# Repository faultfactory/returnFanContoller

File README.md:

# returnFanContoller

### Problem: 

My house has an issue with stratification in the summer, requiring us to leave a fan in the stairwell. I saw this potentially coming from talking to my neighbors and in addition to good insulation on the roof deck, I also installed a return air duct on the 2nd floor (which it did not have).  This duct is very high in the room and with a proper draw should evacuate hot air in the room quickly with the right amount of negative pressure applied. Because the return ducts in the house start with a (very poorly sealed) run of panning through joist bays and the duct takes a circuitous path upstairs, I am confident I am getting very little, if any draw from the return duct I connected to the 2nd floor.  To remedy this I have purchased a [Fantech ProAir EC-6](https://shop.fantech.net/en-US/prioair--6--ec--inline--duct--fan/p96222#!) I chose this because I would rather not play around with dampers if I can help it.  My furnace is not intended to integrate  with any sort of external fan, nor is my thermostat (nest... maybe 2nd gen?). 

### Goals: 

1. Log the activity of the 24VAC thermostat signals coming from the Nest. Also log the blower fan speeds and some relevant temperatures. 
2. Activate the booster fan when the furnace fan runs.
3. Monitor a temp sensor on the second floor and activate both the furnace and booster fan when the temperature differential exceeds a threshold. 

~~This repostitory consists of the code for the controller which will run on a raspberry pi. Schematics / BOM  will be on a separate hackaday.io project when time permits.~~

This project has been completed and I am in the process of documenting it. Overwhelming success. However, it was exceptionally difficult to get a proper PWM generated out of the raspberry pi and over time it just became more trouble than it was worth to stay with that platform. I've moved the effort to an Arduino which worked fine. I am still going to attempt to add some of the bells and whistles I wanted earlier but for now it works great.

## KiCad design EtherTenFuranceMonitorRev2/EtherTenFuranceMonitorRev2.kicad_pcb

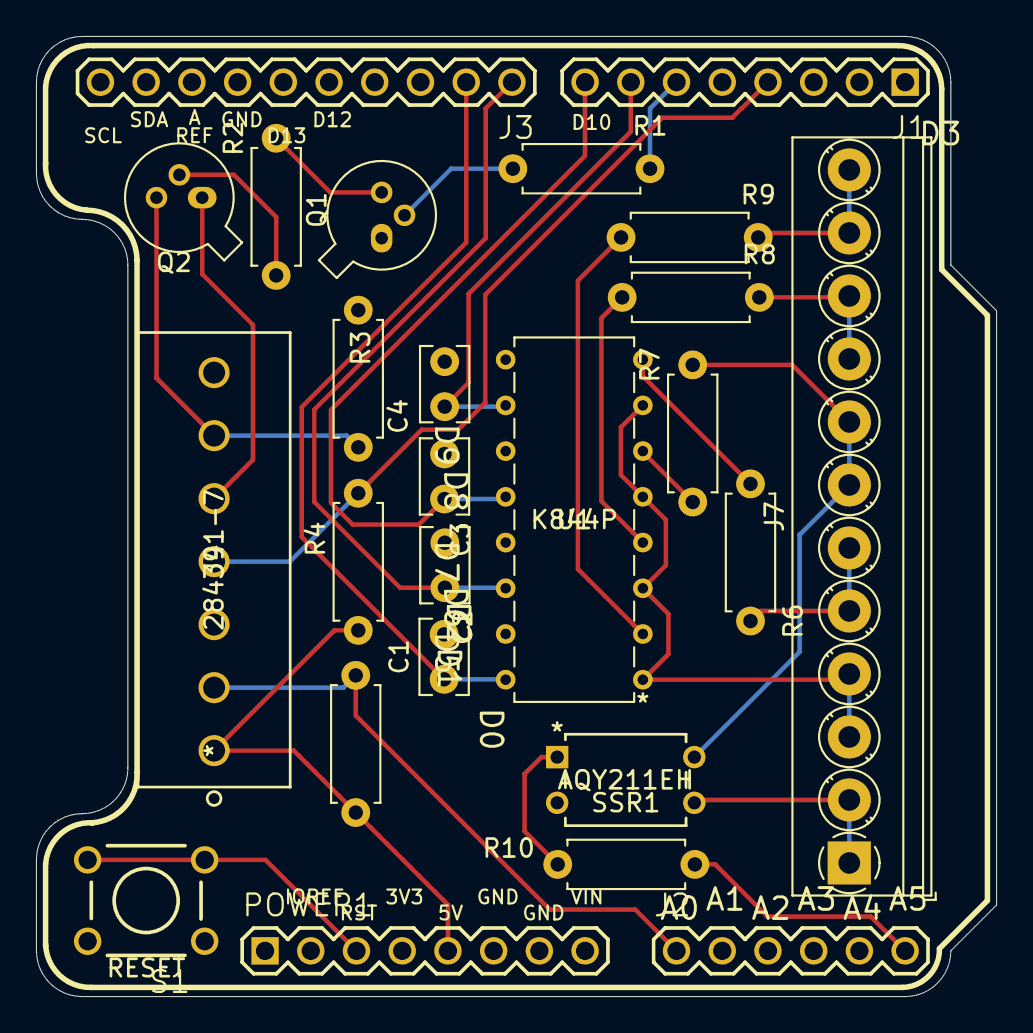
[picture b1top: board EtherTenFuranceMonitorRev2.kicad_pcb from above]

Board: 2 copper layers, 53.3 x 53.3 mm, 25 parts (0 on the bottom side), 27 nets.

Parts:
C1, C2, C3, C4: 0.1uF; C_Rect_L4.0mm_W2.5mm_P2.50mm
J1: Digital_0_7; 1X08
J2: Analog; 1X06
J3: Digital_8_13; 1X10
J4: 284391-7
J7: Screw_Terminal_01x12; TerminalBlock_Phoenix_PT-1,5-12-3.5-H_1x12_P3.50mm_Horizont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
POWER1: Power; 1X08
Q1: 2N2222A; TO-18-3
Q2: 2N2907A; TO-18-3
R0, R6, R7, R8, R9: 4.7K; R_Axial_DIN0207_L6.3mm_D2.5mm_P7.62mm_Horizontal
R1: 4.7k; R_Axial_DIN0207_L6.3mm_D2.5mm_P7.62mm_Horizontal
R2: 33k; R_Axial_DIN0207_L6.3mm_D2.5mm_P7.62mm_Horizontal
R3: 15k; R_Axial_DIN0207_L6.3mm_D2.5mm_P7.62mm_Horizontal
R4: 5.6k; R_Axial_DIN0207_L6.3mm_D2.5mm_P7.62mm_Horizontal
R10: 1k; R_Axial_DIN0207_L6.3mm_D2.5mm_P7.62mm_Horizontal
S1: RESET; TACTILE-PTH
SSR1: AQY211EH
U1: K844P

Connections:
/5V: J4.1, POWER1.5, R0.1, R4.1
/24VAC_COM: J7.3, J7.4, U1.1, U1.3, U1.5, U1.7
/24VAC_COOL: J7.9, J7.10, R8.2
/24VAC_FAN: J7.7, J7.8, R7.2, SSR1.4
/24VAC_HEAT: J7.11, J7.12, R9.2
/24VAC_HUM: J7.5, J7.6, R6.2
/24VAC_PWR: J7.1, J7.2, SSR1.3
/A0: J2.1, J4.2, R0.2
/A5: J2.6, R10.2
/BOOSTER10V: J4.5, Q2.1
/BOOSTERCTRL: J4.6, Q2.3, R3.2
/BOOSTERTACH: J1.4, J4.4, R4.2
/D5: J1.6, R1.2
/D6: C4.1, J1.7, U1.10
/D7: C3.1, J1.8, U1.12
/D8: C2.1, J3.1, U1.14
/D9: C1.1, J3.2, U1.16
/RESET: POWER1.3, S1.3, S1.4
GND: C1.2, C2.2, C3.2, C4.2, J3.7, J4.3, J4.7, POWER1.6, POWER1.7, Q1.1, R3.1, S1.1, S1.2, SSR1.2, U1.9, U1.11, U1.13, U1.15
unnamed: Q1.2, R1.1
unnamed: Q1.3, R2.2
unnamed: Q2.2, R2.1
unnamed: R6.1, U1.8
unnamed: R7.1, U1.6
unnamed: R8.1, U1.4
unnamed: R9.1, U1.2
unnamed: R10.1, SSR1.1

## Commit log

2020-02-05 initial file commit
2020-02-05 cmake version change
2021-12-30 Added note
2022-01-02 adding ethernet pins
2022-09-12 pulling all project comonents together for cleanup
2022-09-12 tweak to readme to trigger vscode

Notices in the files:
parts and their libraries:
Copyright 2021 Accelerated Designs. All rights reserved.
Copyright 2016 Accelerated Designs. All rights reserved.
